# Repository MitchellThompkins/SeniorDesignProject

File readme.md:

## Description

This contains a sample of one of the PCBs, the lifting mechanism portion, utilized in our 2013 Senior Design Project titled “Inquiry into the Implementation of a Low-Power Mobile Sorting System for Polychromatic Discrimination of Differently Sized Objects” and entered into the 2013 IEEE SouthEastCon. Also shown below is a shot of the final project. This was designed on an extremely limited budget and necessitated the creative repurposing of some common devices and components.

### Lifting mechanism PCB:

### Side view of finished project:

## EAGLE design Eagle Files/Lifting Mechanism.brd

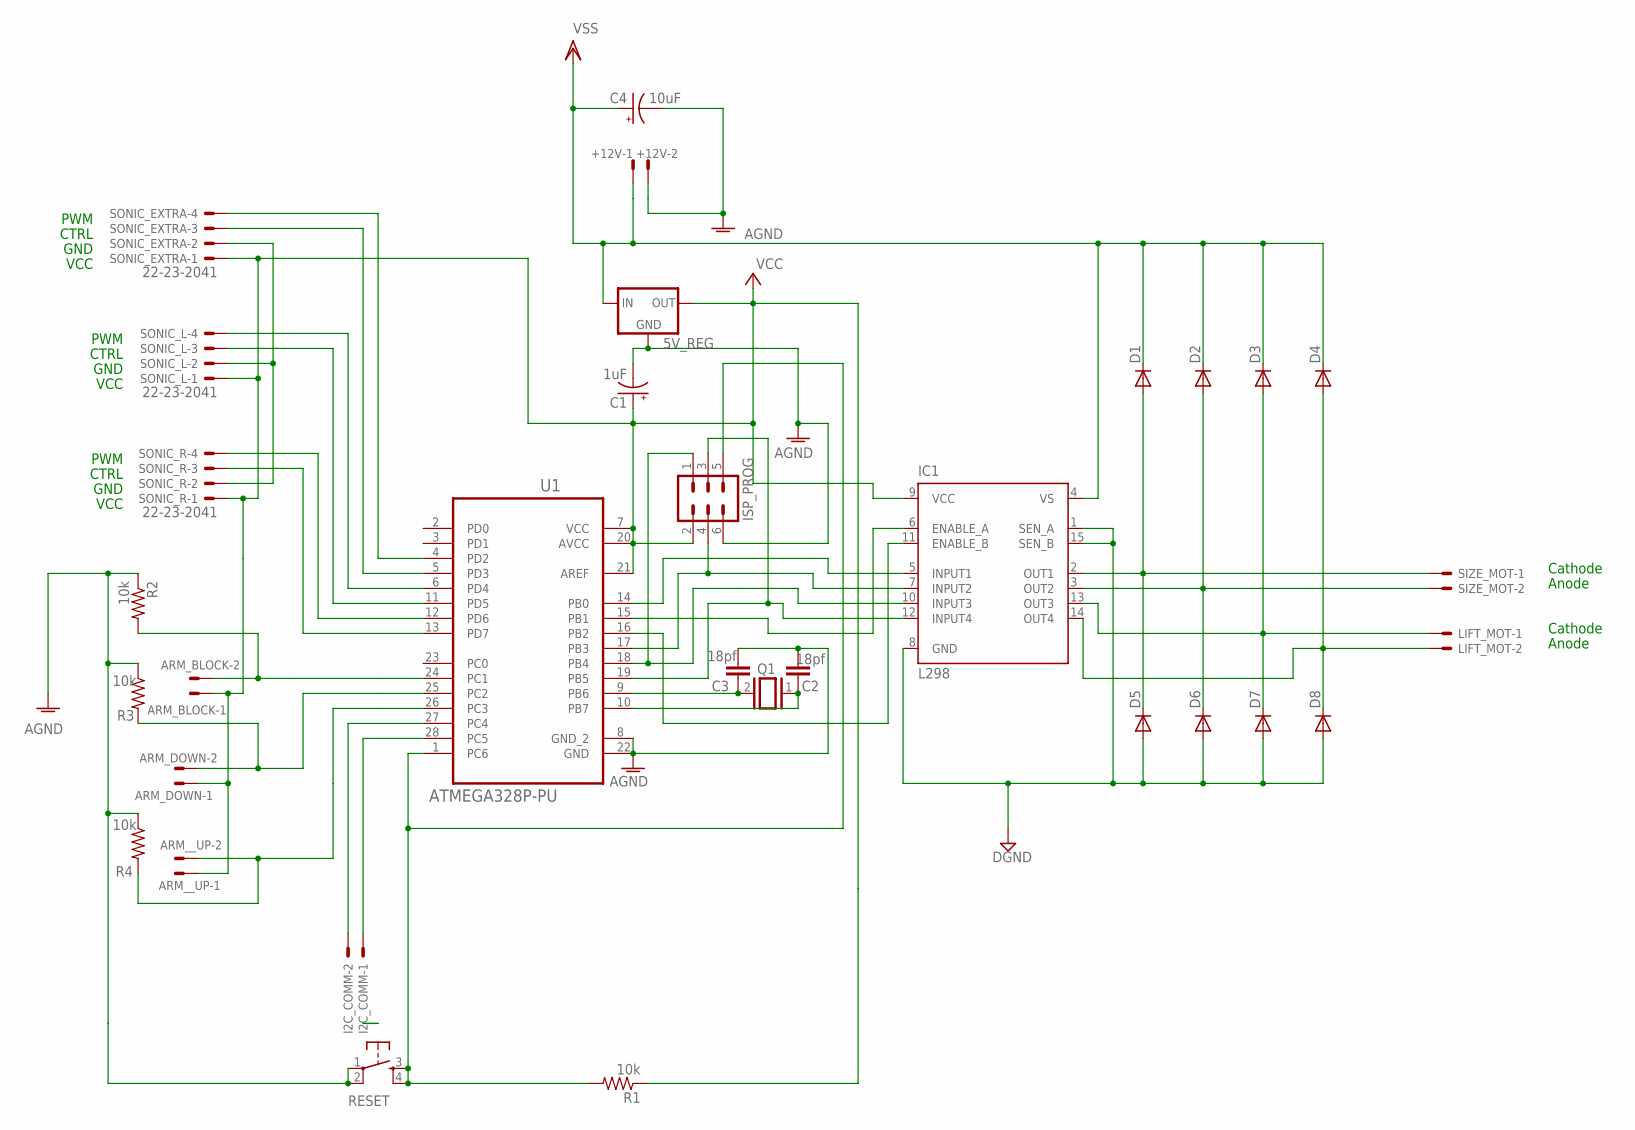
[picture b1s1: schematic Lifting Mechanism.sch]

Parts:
5V_REG: V_REG_78XXSINK; TO220-IGO
+12V: 22-23-2021
ARM_BLOCK: 22-23-2021
ARM_DOWN: 22-23-2021
ARM__UP: 22-23-2021
C1: 1uF; E2,5-5
C2, C3: 18pf; C2.5-3
C4: 10uF; E2,5-5
D1, D2, D3, D4, D5, D6, D7, D8: DIODE1N4148; DIODE-1N4148
I2C_COMM: 22-23-2021
IC1: L298; MULTIWATT-15
ISP_PROG: MA03-2
LIFT_MOT: 22-23-2021
Q1: XTAL/S; QS
R1, R2, R3, R4: 10k; 0207/7
RESET: TAC_SWITCHPTH; TACTILE-PTH
SIZE_MOT: 22-23-2021
SONIC_EXTRA: 22-23-2041
SONIC_L: 22-23-2041
SONIC_R: 22-23-2041
U1: ATMEGA328P-PU; DIP254P762X457-28

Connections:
GND: 5V_REG.GND, +12V.2, C1.-, C2.2, C3.2, C4.-, D5.A, D6.A, D7.A, D8.A, IC1.1 (SEN_A), IC1.8 (GND), IC1.15 (SEN_B), ISP_PROG.6, R2.1, R3.1, R4.1, RESET.1, RESET.2, U1.8 (GND_2), U1.22 (GND)
unnamed: ARM_BLOCK.2, R2.2, U1.24 (PC1)
unnamed: ARM_DOWN.2, R3.2, U1.25 (PC2)
unnamed: I2C_COMM.1, U1.28 (PC5)
unnamed: C3.1, Q1.2, U1.9 (PB6)
unnamed: IC1.5 (INPUT1), U1.14 (PB0)
unnamed: D2.A, D6.C, IC1.3 (OUT2), SIZE_MOT.2
unnamed: I2C_COMM.2, U1.27 (PC4)
unnamed: D4.A, D8.C, IC1.14 (OUT4), LIFT_MOT.2
unnamed: C2.1, Q1.1, U1.10 (PB7)
unnamed: ARM__UP.2, R4.2, U1.26 (PC3)
unnamed: SONIC_R.3, U1.13 (PD7)
unnamed: SONIC_EXTRA.2, SONIC_L.2, SONIC_R.2
unnamed: SONIC_R.4, U1.12 (PD6)
unnamed: SONIC_L.3, U1.11 (PD5)
unnamed: SONIC_L.4, U1.6 (PD4)
unnamed: SONIC_EXTRA.3, U1.5 (PD3)
unnamed: ISP_PROG.5, R1.2, RESET.3, RESET.4, U1.1 (PC6)
unnamed: SONIC_EXTRA.4, U1.4 (PD2)
unnamed: D3.A, D7.C, IC1.13 (OUT3), LIFT_MOT.1
unnamed: IC1.10 (INPUT3), ISP_PROG.1, U1.18 (PB4)
unnamed: IC1.6 (ENABLE_A), U1.15 (PB1)
unnamed: IC1.11 (ENABLE_B), U1.16 (PB2)
unnamed: IC1.7 (INPUT2), ISP_PROG.4, U1.17 (PB3)
unnamed: IC1.12 (INPUT4), ISP_PROG.3, U1.19 (PB5)
unnamed: D1.A, D5.C, IC1.2 (OUT1), SIZE_MOT.1
VCC: 5V_REG.OUT, ARM_BLOCK.1, ARM_DOWN.1, ARM__UP.1, C1.+, IC1.9 (VCC), ISP_PROG.2, R1.1, SONIC_EXTRA.1, SONIC_L.1, SONIC_R.1, U1.7 (VCC), U1.20 (AVCC), U1.21 (AREF)
VSS: 5V_REG.IN, +12V.1, C4.+, D1.C, D2.C, D3.C, D4.C, IC1.4 (VS)

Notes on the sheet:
Cathode
Anode
VCC
GND
CTRL
PWM

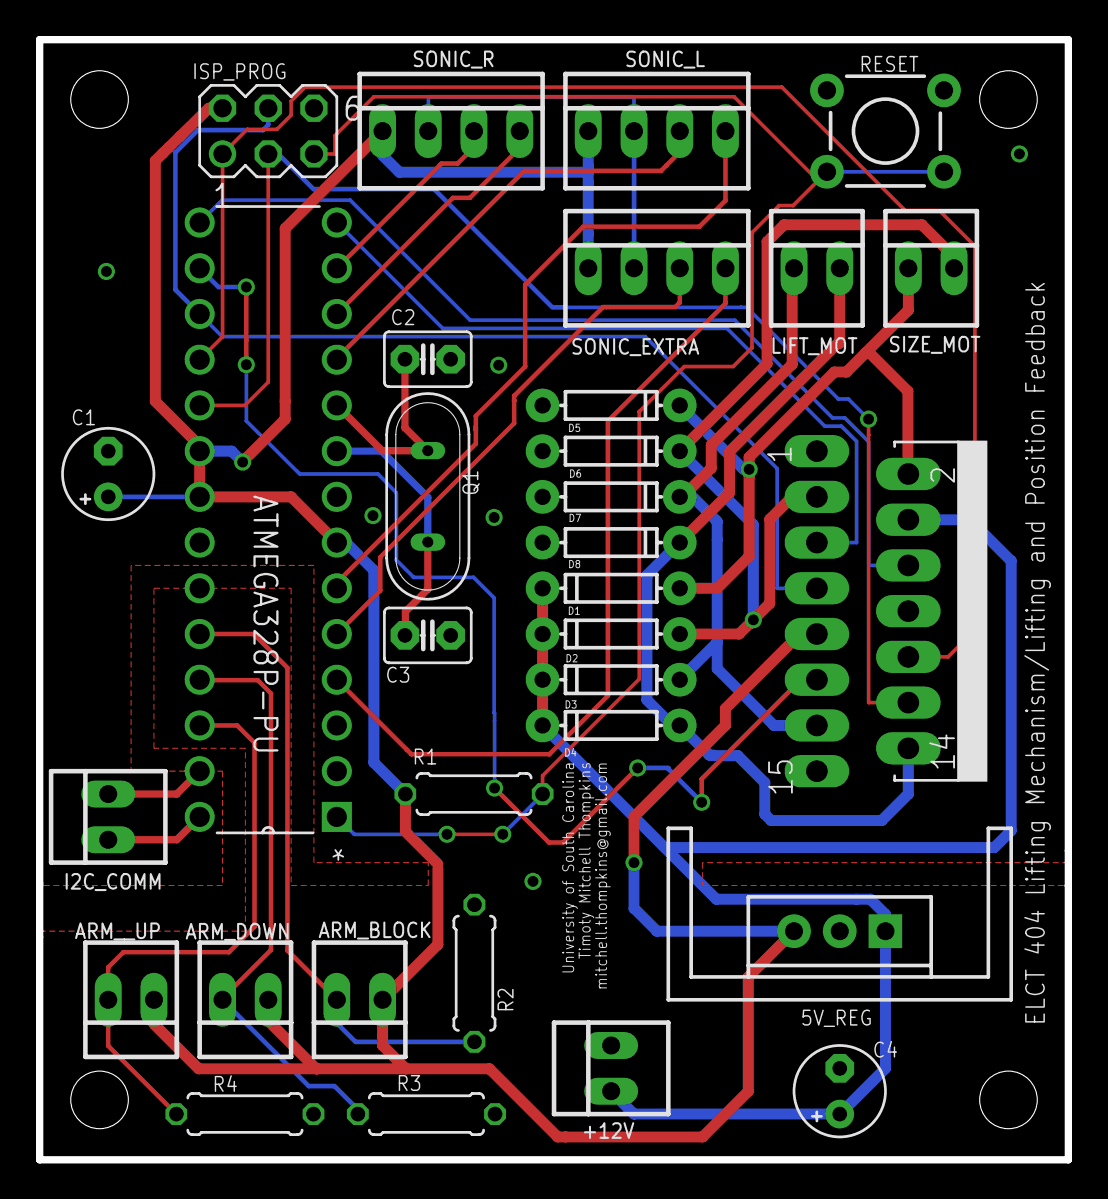
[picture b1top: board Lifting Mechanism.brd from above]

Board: 2 copper layers, 57.1 x 62.2 mm, 32 parts (0 on the bottom side), 28 nets.

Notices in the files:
parts and their libraries:
SparkFun: Licensing: CC v3.0 Share-Alike You are welcome to use this library for commercial purposes.
